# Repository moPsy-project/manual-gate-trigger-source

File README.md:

# Manual Gate/Trigger Source

> Eurorack Module for a manual gate/trigger source

## Dependencies

This project uses symbols from the [moPsy-KiCad-resources](https://github.com/moPsy-project/moPsy-KiCad-resources).

## License

This work is licensed under a [Creative Commons Attribution-ShareAlike 4.0 International License](http://creativecommons.org/licenses/by-sa/4.0/).

BY: Stefan Haun (mail@tuxathome.de)

See [LICENSE.txt](LICENSE.txt) for details.

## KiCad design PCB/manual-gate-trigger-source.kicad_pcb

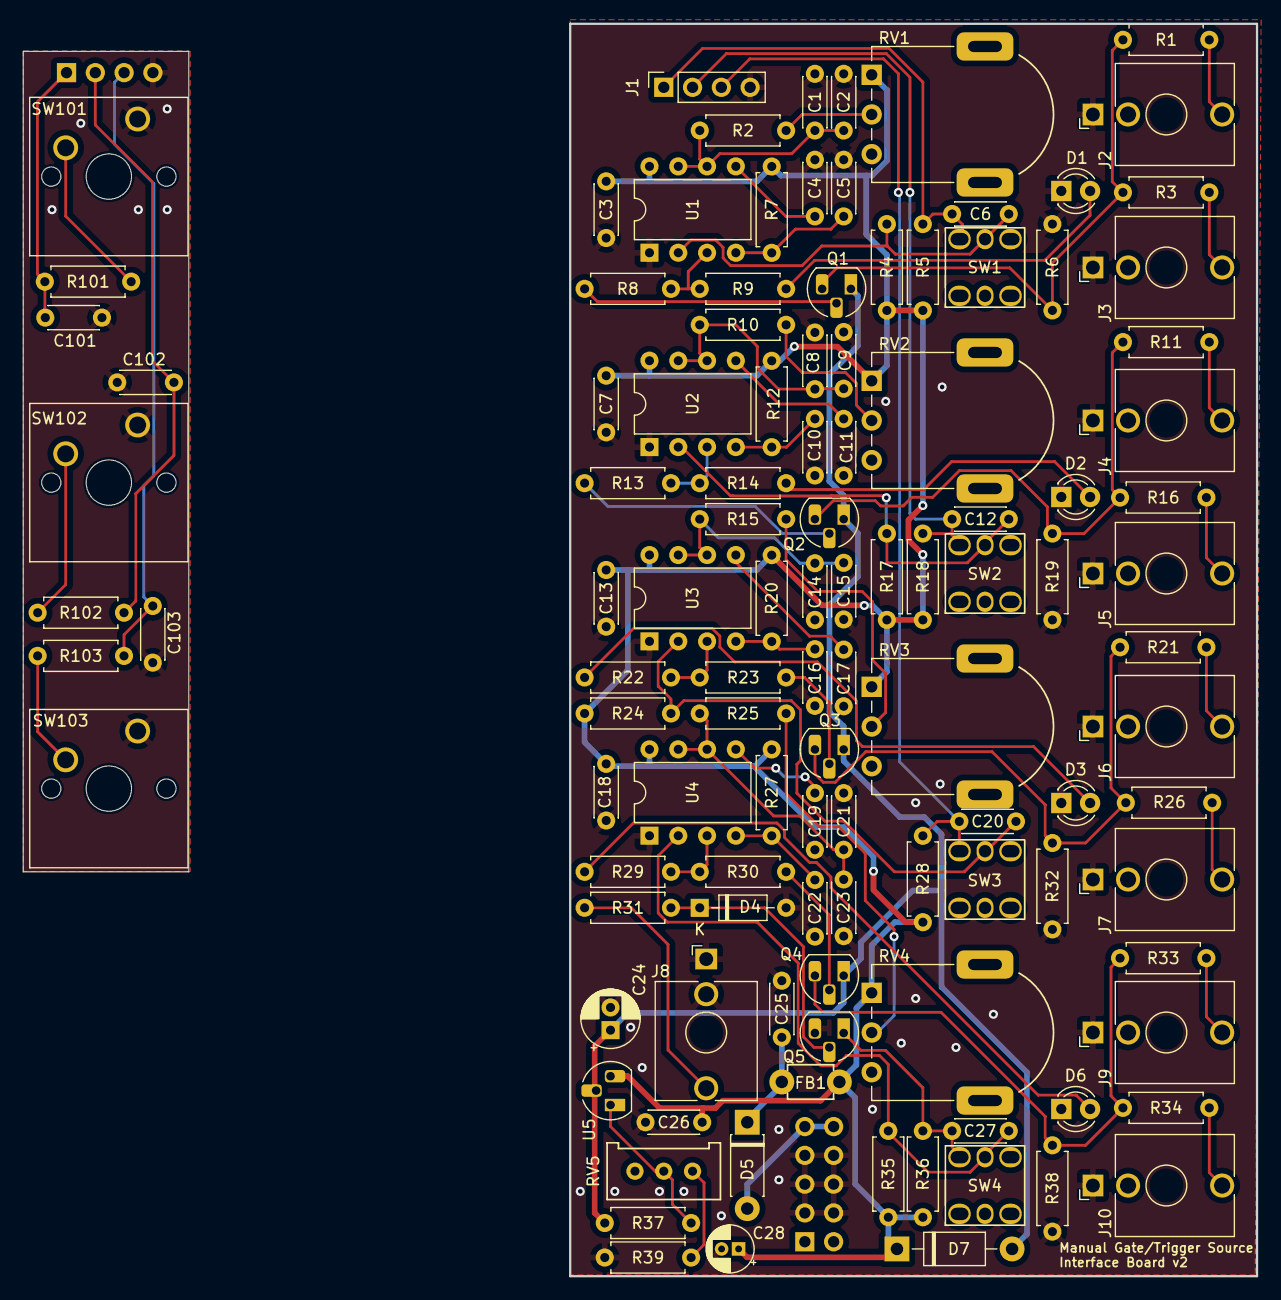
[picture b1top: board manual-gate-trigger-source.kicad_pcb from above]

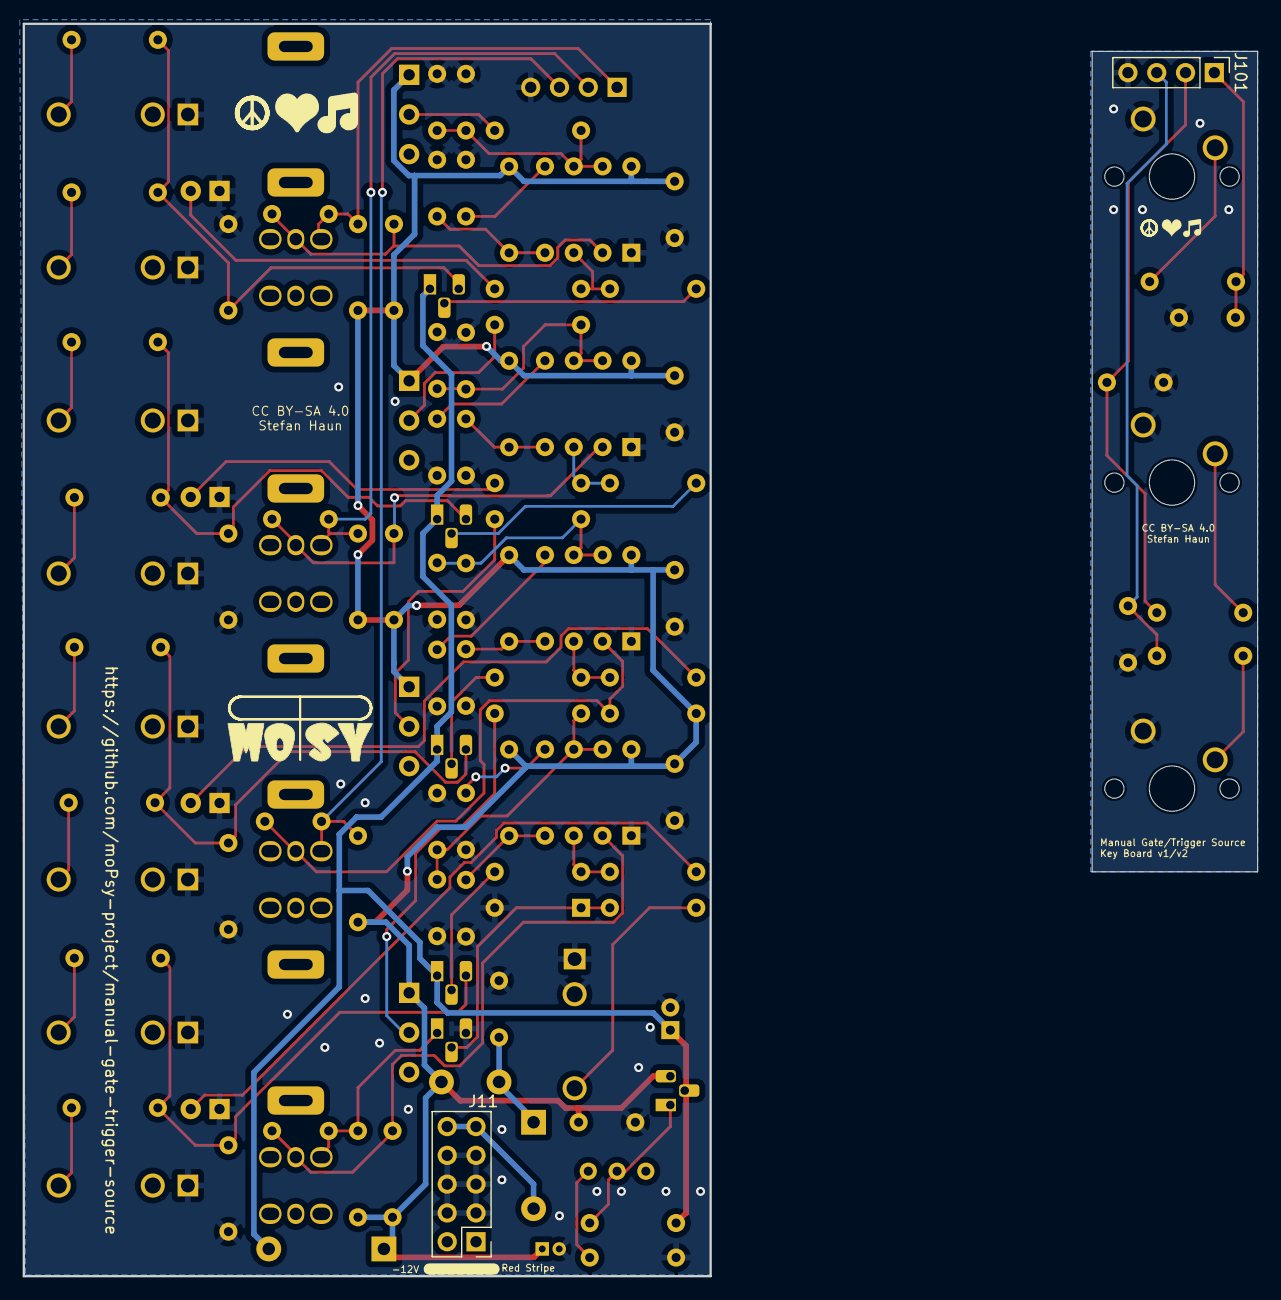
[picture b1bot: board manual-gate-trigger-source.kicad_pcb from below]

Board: 2 copper layers, 60.6 x 110.5 mm, 115 parts (2 on the bottom side), 63 nets.

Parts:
C1, C2, C3, C5, C7, C8, C9, C10, C13, C14, C15, C16, C18, C21, C22, C23, C25, C26, C101, C102, C103: 100n; C_Disc_D4.3mm_W1.9mm_P5.00mm
C4, C6, C11, C12, C17, C19, C20, C27: 10n; C_Disc_D4.3mm_W1.9mm_P5.00mm
C24: 1u; CP_Radial_D5.0mm_P2.00mm
C28: 10u; CP_Radial_D4.0mm_P1.50mm
D1, D2, D3, D6: rt; LED_D3.0mm
D4: 1N4148; D_DO-35_SOD27_P7.62mm_Horizontal
D5: D_Schottky; D_DO-41_SOD81_P7.62mm_Horizontal
D7: 1N4002; D_DO-41_SOD81_P10.16mm_Horizontal
FB1: FerriteBead; FBeadL4D4
J1: Conn_01x04; PinSocket_1x04_P2.54mm_Vertical
J2, J4, J6, J9: OUTa; Jack_3.5mm_QingPu_WQP-PJ398SM_Vertical_CircularHoles_Center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
J3, J5, J7, J10: OUTb; Jack_3.5mm_QingPu_WQP-PJ398SM_Vertical_CircularHoles_Center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
J8: IN1; Jack_3.5mm_QingPu_WQP-PJ398SM_Vertical_CircularHoles_Center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
J11: PWR; PinHeader_2x05_P2.54mm_Vertical
J101: Conn_01x04; PinHeader_1x04_P2.54mm_Vertical
Q1, Q2, Q3, Q4, Q5: BC547; TO-92_HandSolder
R1, R3, R11, R16, R21, R26, R33, R34: 1k; R_Axial_DIN0207_L6.3mm_D2.5mm_P7.62mm_Horizontal
R2, R10, R15, R25: 4k7; R_Axial_DIN0207_L6.3mm_D2.5mm_P7.62mm_Horizontal
R4, R6, R7, R12, R17, R19, R20, R24, R27, R31, R32, R35, R38: 10k; R_Axial_DIN0207_L6.3mm_D2.5mm_P7.62mm_Horizontal
R5, R8, R13, R18, R23, R28, R30, R36: 2k2; R_Axial_DIN0207_L6.3mm_D2.5mm_P7.62mm_Horizontal
R9, R14, R22, R29, R39: 470R; R_Axial_DIN0207_L6.3mm_D2.5mm_P7.62mm_Horizontal
R37: 330R; R_Axial_DIN0207_L6.3mm_D2.5mm_P7.62mm_Horizontal
R101, R102, R103: 100R; R_Axial_DIN0207_L6.3mm_D2.5mm_P7.62mm_Horizontal
RV1, RV2, RV3, RV4: 1M; Potentiometer_Befaco_12mm_Single_Vertical
RV5: 2k; Suntan 3296 Trim Pot
SW1, SW2, SW3, SW4: ON/ON; PB_Hor_7x7_2pole_hybrid
SW101, SW102, SW103: SW_Push; SW_Cherry_MX_1.00u_PCB
U1, U2, U3, U4: LM555xN; DIP-8_W7.62mm
U5: LM317L_TO92; TO-92_HandSolder

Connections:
+12V: C3.1, C7.1, C13.1, C18.1, C26.1, C28.1, D7.1 (K), FB1.2, R4.2, R5.2, R7.2, R12.2, R17.2, R18.2, R20.2, R24.2, R27.2, R28.2, R35.2, R36.2, RV1.1, RV2.1, RV3.1, RV4.1, U1.8 (VCC), U2.8 (VCC), U3.8 (VCC), U4.8 (VCC), U5.3 (VI)
/+12V_DIR: C25.1, D5.1 (K), FB1.1
/+12V_IN: D5.2 (A), J11.9, J11.10
/CV Input/TRIGGER_IN: C27.1, Q5.1 (C), R36.1, SW4.2 (B)
/Gate Length Generator 1/TRIGGER_IN: C6.1, J1.1, R5.1, SW1.2 (B)
/Gate Length Generator 1/TRIGGER_OUT: R8.1, R9.2, U1.3 (Q)
/Gate Length Generator 2/TRIGGER_IN: C12.1, J1.2, R18.1, SW2.2 (B)
/Gate Length Generator 2/TRIGGER_OUT: R13.1, R14.2, U2.3 (Q)
/Gate Length Generator 3/TRIGGER_IN: C20.1, J1.3, R28.1, SW3.2 (B)
/Gate Length Generator 3/TRIGGER_OUT: R22.2, R23.1, U3.3 (Q)
/Gate Length Generator 4/TRIGGER_OUT: R29.2, R30.1, U4.3 (Q)
/Manual Input 1/TRIGGER_IN: C101.2, J101.1, R101.2
/Manual Input 2/TRIGGER_IN: C102.2, J101.2, R102.2
/Manual Input 3/TRIGGER_IN: C103.2, J101.3, R103.2
GND: C1.2, C2.2, C3.2, C4.2, C5.2, C7.2, C8.2, C9.2, C10.2, C11.2, C13.2, C14.2, C15.2, C16.2, C17.2, C18.2, C19.2, C21.2, C22.2, C23.2, C24.2, C25.2, C26.2, C28.2, C101.1, C102.1, C103.1, D1.1 (K), D2.1 (K), D3.1 (K), D4.2 (A), D6.1 (K), J1.4, J2.S, J3.S, J4.S, J5.S, J6.S, J7.S, J8.S, J8.TN, J9.S, J10.S, J11.3, J11.4, J11.5, J11.6, J11.7, J11.8, J101.4, Q5.3 (E), R6.1, R19.1, R32.1, R38.1, R39.2, SW101.1, SW102.1, SW103.1, U1.1 (GND), U2.1 (GND), U3.1 (GND), U4.1 (GND)
unnamed: D1.2 (A), R9.1
unnamed: D2.2 (A), R14.1
unnamed: D3.2 (A), R22.1
unnamed: D4.1 (K), Q5.2 (B), R31.2
unnamed: D6.2 (A), R29.1
unnamed: J2.T, R1.2
unnamed: J3.T, R3.2
unnamed: J4.T, R11.2
unnamed: J5.T, R16.2
unnamed: J6.T, R21.2
unnamed: J7.T, R26.2
unnamed: J8.T, R31.1
unnamed: J9.T, R33.2
unnamed: J10.T, R34.2
unnamed: Q1.2 (B), R8.2
unnamed: Q1.3 (E), R1.1, R3.1, R6.2
unnamed: Q2.2 (B), R13.2
unnamed: Q2.3 (E), R11.1, R16.1, R19.2
unnamed: Q3.2 (B), R23.2
unnamed: Q3.3 (E), R21.1, R26.1, R32.2
unnamed: Q4.2 (B), R30.2
unnamed: Q4.3 (E), R33.1, R34.1, R38.2
unnamed: R2.2, RV1.2
unnamed: R10.2, RV2.2
unnamed: R15.2, RV3.2
unnamed: R25.2, RV4.2
unnamed: R39.1, RV5.1
unnamed: R101.1, SW101.2
unnamed: R102.1, SW102.2
unnamed: R103.1, SW103.2
unnamed: C6.2, R4.1, SW1.1 (A), U1.2 (TR)
unnamed: C12.2, R17.1, SW2.1 (A), U2.2 (TR)
unnamed: C20.2, R24.1, SW3.1 (A), U3.2 (TR)
unnamed: C27.2, R35.1, SW4.1 (A), U4.2 (TR)
unnamed: C4.1, U1.5 (CV)
unnamed: C1.1, C2.1, R2.1, U1.6 (THR), U1.7 (DIS)
unnamed: C5.1, R7.1, U1.4 (R)
unnamed: C11.1, U2.5 (CV)
unnamed: C8.1, C9.1, R10.1, U2.6 (THR), U2.7 (DIS)
unnamed: C10.1, R12.1, U2.4 (R)
unnamed: C17.1, U3.5 (CV)
unnamed: C14.1, C15.1, R15.1, U3.6 (THR), U3.7 (DIS)
unnamed: C16.1, R20.1, U3.4 (R)
unnamed: C19.1, U4.5 (CV)
unnamed: C21.1, C23.1, R25.1, U4.6 (THR), U4.7 (DIS)
unnamed: C22.1, R27.1, U4.4 (R)
unnamed: R37.2, RV5.2, U5.1 (ADJ)
Vdrive: C24.1, D7.2 (A), Q1.1 (C), Q2.1 (C), Q3.1 (C), Q4.1 (C), R37.1, U5.2 (VO)

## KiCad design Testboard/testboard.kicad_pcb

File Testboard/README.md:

# Testboard

> Testboard for the Eurorack Module for a manual gate/trigger source

As described in #53, buttons do not always trigger reliably after a cold start,
i.e. a longer period without power.

This happens on all buttons, but only in the finished circuit. The effect could not be observed on the breadboard and is therefore hard to debug.

This board contains only one trigger and some testpoints.

It is meant to be connected to the [Eurorack Power Breakout](https://github.com/moPsy-project/eurorack-power-breakout).

## Dependencies

This project uses symbols from the [moPsy-KiCad-resources](https://github.com/moPsy-project/moPsy-KiCad-resources).

## License

This work is licensed under a [Creative Commons Attribution-ShareAlike 4.0 International License](http://creativecommons.org/licenses/by-sa/4.0/).

BY: Stefan Haun (mail@tuxathome.de)

See [LICENSE.txt](LICENSE.txt) for details.

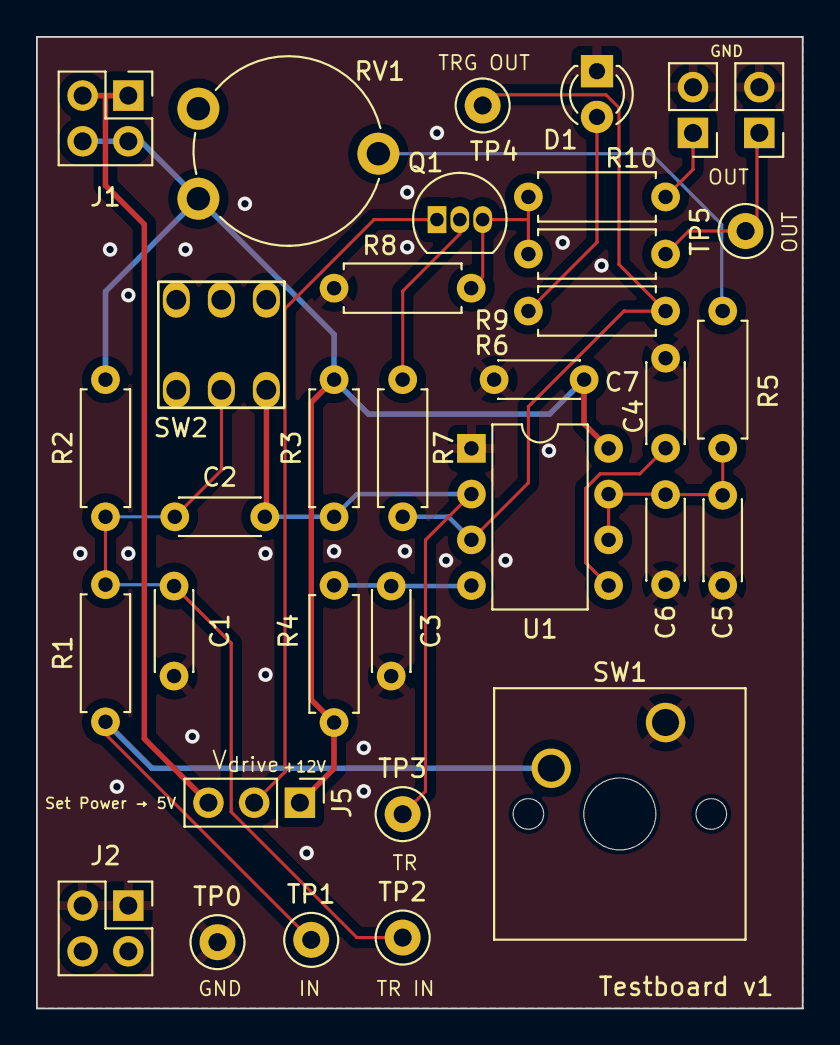
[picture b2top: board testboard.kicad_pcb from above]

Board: 2 copper layers, 42.5 x 54.0 mm, 34 parts (0 on the bottom side), 17 nets.

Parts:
C1, C3, C5, C6, C7: 100n; C_Disc_D4.3mm_W1.9mm_P5.00mm
C2, C4: 10n; C_Disc_D4.3mm_W1.9mm_P5.00mm
D1: rt; LED_D3.0mm
J1: upper; PinSocket_2x02_P2.54mm_Vertical
J2: lower; PinSocket_2x02_P2.54mm_Vertical
J3, J4: Out; PinHeader_1x02_P2.54mm_Vertical
J5: V_{drive}; PinHeader_1x03_P2.54mm_Vertical
Q1: BC547; TO-92_Inline
R1: 100R; R_Axial_DIN0207_L6.3mm_D2.5mm_P7.62mm_Horizontal
R2, R7: 2k2; R_Axial_DIN0207_L6.3mm_D2.5mm_P7.62mm_Horizontal
R3, R4, R8: 10k; R_Axial_DIN0207_L6.3mm_D2.5mm_P7.62mm_Horizontal
R5: 4k7; R_Axial_DIN0207_L6.3mm_D2.5mm_P7.62mm_Horizontal
R6: 470R; R_Axial_DIN0207_L6.3mm_D2.5mm_P7.62mm_Horizontal
R9, R10: 1k; R_Axial_DIN0207_L6.3mm_D2.5mm_P7.62mm_Horizontal
RV1: 1M; Potentiometer_Piher_PT-10-V10_Vertical
SW1: SW_Push; SW_Cherry_MX_1.00u_PCB
SW2: ON/ON; PB_Hor_7x7_2pole_2.5mm
TP0: GND; TestPoint_Loop_D1.80mm_Drill1.0mm_Beaded
TP1: IN; TestPoint_Loop_D1.80mm_Drill1.0mm_Beaded
TP2: TRIGGER_IN; TestPoint_Loop_D1.80mm_Drill1.0mm_Beaded
TP3: TR; TestPoint_Loop_D1.80mm_Drill1.0mm_Beaded
TP4: TRIGGER_OUT; TestPoint_Loop_D1.80mm_Drill1.0mm_Beaded
TP5: OUT; TestPoint_Loop_D1.80mm_Drill1.0mm_Beaded
U1: LM555xN; DIP-8_W7.62mm

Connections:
+12V: C7.1, J1.3, J1.4, J5.1, R2.2, R3.2, R4.2, RV1.1, U1.8 (VCC)
/TRIGGER_IN: C1.2, C2.1, R1.2, R2.1, SW2.1 (A), TP2.1
/TRIGGER_OUT: R6.2, R7.1, TP4.1, U1.3 (Q)
GND: C1.1, C3.2, C4.2, C5.2, C6.2, C7.2, D1.1 (K), J2.1, J2.2, J3.2, J4.2, R8.1, SW1.1, TP0.1, U1.1 (GND)
unnamed: D1.2 (A), R6.1
unnamed: J3.1, R9.2, TP5.1
unnamed: J4.1, R10.2
unnamed: J5.2, Q1.1 (C)
unnamed: Q1.2 (B), R7.2
unnamed: Q1.3 (E), R8.2, R9.1, R10.1
unnamed: R1.1, SW1.2, TP1.1
unnamed: R5.2, RV1.2
unnamed: C2.2, R3.1, SW2.2 (B), TP3.1, U1.2 (TR)
unnamed: C4.1, U1.5 (CV)
unnamed: C5.1, C6.1, R5.1, U1.6 (THR), U1.7 (DIS)
unnamed: C3.1, R4.1, U1.4 (R)
Vdrive: J1.1, J1.2, J5.3

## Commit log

2022-12-17 :tada: Initial commit
2022-12-17 :money_with_wings: Add FUNDING information
2022-12-17 :construction_worker: Add release workflow
2022-12-17 :see_no_evil: Add gitignore for kicad projects
2022-12-17 :tada: Initial kicad project
2022-12-17 :sparkles: Draft a trigger input
2022-12-28 :sparkles: Draft a trigger output
    Based on http://www.synthpanel.com/modules/cgs24_gatetotrigger.html
    Fixes #1
2022-12-28 :sparkles: Add OPV-based voltage generation and selector
2022-12-29 :art: Change voltage generation to R divider
2022-12-29 :art: Debounce the trigger button
2022-12-29 :sparkles: Add control for minimum gate and trigger length
    https://www.elektronik-kompendium.de/sites/slt/0310121.htm?mr=100330&mc=10u&mth=2%2C42798
2022-12-29 :sparkles: Sort out gate/trigger output
2022-12-29 :sparkles: Set up power supply and filtering
2022-12-29 :sparkles: Add gate length generator based on op-amp
    On op-amp in the TL072 is unused, so build a gate length generator with this
    which may replace the LM555.
    Based on
    https://circuitdigest.com/electronic-circuits/how-to-design-a-simple-monostable-multivibrator-circuit-using-op-amp
    https://www.electronics-tutorials.ws/de/operationsverstarker/operationsverstaerker-monostabil.html
2022-12-30 :page_facing_up: Add LICENSE file for CC BY-SA 4.0
2022-12-30 :page_facing_up: Add License information to README
2023-01-09 :wrench: Select mono jack and switch symbols
    Chosing PJ398SM (Thonkiconn/Befaco).
2023-01-10 :pencil2: Fix input polarity of 555 design
2023-01-10 :hammer: Adjust RC element of 555 gate length generator
    according to
    https://github.com/moPsy-project/manual-gate-trigger-source/issues/9#issuecomment-1377659194
2023-01-10 :fire: Remove the op-amp design for gate length generator
2023-01-10 :memo: Remove todo and fix RC annotation
2023-01-10 :pencil2: Fix HPF for 555 input
    As the signal is one-sided to V+, a second resistor was necessary.
2023-01-10 :hammer: Move gate/trigger selector to 555 section
    This is very specific to the 555 circuit, so it's better displayed
    there.
2023-01-11 :art: Improve the voltage selector circuit
    Use parallel resistors to the upper/lower leg of an 8V divider to switch
    between 5V and 10V with a SPDT switch with middle off position
    Fixes: #4
2023-01-11 :sparkles: Add a drive transistor to the voltage source
    The op-amp alone cannot drive all outputs. Add a transistor as output driver
    and incorporate it into the feedback loop.
2023-01-11 :wrench: Adjust LPF for then voltage selector switch
    Measurements have shown that this is the best value for the switch that
    will most likely be used.
2023-01-11 :bug: Fix output ripple by adding a filter cap
2023-01-11 :bug: Fix missing collector resistor on input transistor
2023-01-11 :hammer: separate input into manual and CV
2023-01-11 :sparkles: Set MX footprint for manual switch
2023-01-11 :art: Replace output by push-pull configuration
2023-01-12 :bug: Fix manual input circuit
2023-01-12 :wrench: Adjust manual input LPF to match voltage selector
2023-01-17 :art: Tune RC values for trigger-length selector
2023-01-17 :art: Tune the switch filters
    Tune the switch filters so that no double triggering will
    happen. (Was an issue when releasing the switch.)
2023-01-17 :hammer: Remove push-pull output
    Push-pull does not perform as expected, go back to the
    tried and tested pull-down resistor, but with a slightly
    lower value. Fall-time is good now.
2023-01-17 :art: Improve op-amp behavior
    Add a resistor divider and reduce base resistor of the driver
    transistor to improve transient behaviour.
    Also remove the capacitor, as this introduces resonance!
2023-01-17 :art: Improve output edge speed
    Improve the output speed by reducing the base resistor.
    Changes switching time from 200ns to 50ns.
2023-01-19 :hammer: Move gate/trigger output to sub-schematic
2023-01-19 :sparkles: Duplicate circuit components and complete schmematic
    Multiply input, gate length generator and output
2023-01-19 :art: Decompose schematic parts for the output
2023-01-19 :hammer: Move gate length generator to sub-schematic
2023-01-19 :hammer: Move CV Input to sub-schematic
2023-01-19 :wrench: Configuration for added sub-schematics
2023-01-19 :hammer: Change voltage generator to LM317
    Improve the voltage source by using an LM317 voltage regulator.
    However, during design it turned out that the dropout voltage is too high.
2023-01-24 :memo: Note dependency to moPsy-KiCad-resources
    These are needed for switch footprints
2023-01-24 :wrench: Set footprint for voltage selection switch
    Fixes: #6
2023-01-24 :wrench: Set footprint for gate/trigger switch
    Change the symbol to match the chosen footprint and set the footprint.
    Fixes: #22
2023-01-24 :money_with_wings: add Ko-Fi to funding
2023-01-25 :wrench: Assign a potentiometer footprint
    Assign footprint for https://shop.befaco.org/potentiometers/279-5x-potentiometer-1m.html
    from the moPsy resources.
    Fixes: #17
2023-03-08 :hammer: Change voltage switch footprint and move KiCad version
    Unfortunately KiCad did all in one move, so this is a compound commit.
    Fixes #6
2023-03-09 :sparkles: Add a manual input schematic sheet
2023-03-09 :hammer: Change inputs to the intended 3 manual 1 CV inputs
    There was a mistake when creating the hierarchical sheets leading to 3 CV
    inputs and one manual input instead of the other way around.
2023-03-09 :sparkles: Add capacitors for 555 ICs
2023-03-09 :wrench: Assign component designators
2023-03-09 :art: Tie the unused op-amp to GND
2023-03-09 :wrench: Assign footprints to all symbols
2023-03-09 :hand: First idea for frontpanel arrangement
2023-03-09 :sparkles: Concept variant 2
2023-03-09 :sparkles: Concept 4
2023-03-09 :sparkles: Concept 3
2023-03-09 :hammer: Concept 3: Turn potis and make control module 4HE
2023-03-09 :sparkles: Add FreeCAD and DXF for the panel outline
    This outline is based on Concept 4
2023-03-09 :sparkles: Concept 2 with courtyards
2023-03-09 :sparkles: Add print design for the front panel
2023-03-10 :art: Improve print design after mock test
2023-03-10 :see_no_evil: Add gitignore for KiCad project
2023-03-10 :tada: Add KiCad project for the frontpanel PCB
2023-03-10 :sparkles: Implement front panel design based on outline/print
2023-03-10 :hammer: Fix SVG for correct rendering in KiCad
2023-03-11 :hammer: Squash panel elements for PCB space
    The top potentiometer was reaching over the PCB outlines and had to be moved
    down. Subsequently the whole designed was quashed together by 3mm to make it
    symmetrical again.
2023-03-11 :hammer: Adjust print to changed positions
2023-03-11 :hammer: Adjust frontpanel to new outline/print
2023-03-11 :sparkles: Set PCB size and UI component placement
2023-03-11 :sparkles: Add PCB layout for the module
2023-03-12 :bug: Fix alignment of labels on print
2023-03-12 :pencil2: Fix designator placement
2023-03-12 :wrench: Adapt resistors to create 3V/5V/8V
    Redesign resistor network for different voltages to fix #26.
    Originally +12V were intended, but this needs extensive changes in the
    schematic, which are not worth the effort here. 8V are provided instead
    to model the usual trigger levels.
2023-03-13 :bug: Fix a missing connection
2023-03-15 :hammer: Remove R6 and R7
    The resistors around the V_drive transistor are not needed with this op-amp
    circuit
2023-03-15 :hammer: Tie V_drive op-amp to GND instead of -12V
    This op-amp only needs to go down to 3V, so -12V are not needed.
    This was the only device using the negative rail.
2023-03-15 :fire: Remove -12V rail
2023-03-15 :hammer: Adapt PCB to circuit changes
2023-04-04 :construction_worker: Update checkout in release workflow to v3
2023-04-04 :pencil2: Fix switch cutout dimensions
    adding 0.5mm to the height to accomodate the clips.
2023-04-04 :art: Increase LED hole diameter
2023-04-04 :art: Decrease length of mounting holes
2023-04-04 :pencil: Decrease LED hole diameter - 3.5mm was too much
2023-04-04 :bento: Update DXF export for outline
2023-04-04 :pencil2: Fix print according to corrected cutouts
2023-04-04 :pencil2: Fix frontpanel PCB according to new print and outline
2023-04-04 :pencil2: Fix mirrored URI
2023-04-04 :art: Improve positioning and size of some silk screen elements
2023-04-04 :art: State voltage range on adjustment pots
    Use "lower", "middle", "upper" instead of actual values, as these might
    be changed during assembly by chosing different resistors.
2023-04-04 :pencil2: Adjust to fixed poti footprint
    Adjust to fixed footprint from https://github.com/moPsy-project/moPsy-KiCad-resources/pull/14
2023-04-12 :wrench: Change voltage switch footprint to flush version
    This version has been introduced in
    https://github.com/moPsy-project/moPsy-KiCad-resources/pull/16
    for this purpose.
2023-04-12 :hammer: Adjust PCB layout for changed footprint
2023-04-20 :tada: Add a README for the testboard
2023-04-20 :see_no_evil: Add a gitignore for the KiCAD project
2023-04-20 :tada: Add a KiCAD project for the testboard
2023-04-20 :sparkles: Create the schematic for the testboard
    Mostly copied from the original schematic.
2023-04-20 :sparkles: PCB layout for the testboard
2023-04-20 :bento: Additional KiCAD project files
2023-04-21 :art: Add a GND testpoint for oscilloscope measurements
2023-04-21 :art: Use +5V input as V_drive
    If the pwr breakout is not set correctly, V_drive will be GND, but
    not lead to any issues.
2023-04-21 :hammer: Adapt PCB to schematic changes
2023-05-19 :hammer: Change PCB layout to match new schematic
    This also fixes #46
2023-05-19 :hammer: Replace voltage switch by adjustable voltage regulator
    This fixes #41 and #44
2023-05-19 :hammer: Change transistor footprints to hand-solder variant
    This fixes #56
2023-05-20 :hammer: Change switch footprints to hybrid version
    This allows more flexibility when sourcing the switches
    Fixes: #43
2023-05-20 :rocket: Update the revision number
2023-05-20 :memo: Geographically reannotate the PCB
2023-06-06 :green_heart: Fix runner for release workflow
    ubuntu 18.04 is no longer available
